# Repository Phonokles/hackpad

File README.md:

# ascii-emotion-controller

A macropad for switching the expressions of my ASCII character while
streaming or recording. Built for Hack Club Stardance.

## Why

I have a small face tracking app that renders an ASCII face and animates it
from my webcam and mic. The face sits on top of my stream in OBS, so the
browser window is never the focused one. Keystrokes always land somewhere
else, no matter what I press.

So the hackpad does not show up as a keyboard. It sends lines over USB
serial instead, and the page reads them with WebSerial. That works no matter
which window is in front.

## What is in it

* Seeed XIAO RP2040
* 3 Cherry MX switches
* 1 EC11 rotary encoder with push button
* 1 SSD1306 OLED, 0.91 inch, 128x32, over I2C
* 74 x 75 mm, two layers, solid ground pour
* Case is two printed parts, held together with M3 heatset inserts

Full part list in [BOM.csv](BOM.csv).

## Case

The base is a 8 mm tray with four 3 mm posts that hold the board off the
floor so the solder joints have room. The top plate is 1.5 mm thick around
the switch cutouts, which is what MX clips need to snap in.

## Controls

| Input | does |
| --- | --- |
| SW1 | normal `[+_+]` |
| SW2 | laughing `[*_*]` |
| SW3 | bored `[-_-]` |
| Turn wheel | opens the menu on the OLED |
| Press wheel in menu | confirm selection |
| Hold wheel | mouth keeps moving even when I am quiet |

The menu has auto, normal, laughing, bored, record and transparent.

## Protocol

The XIAO sends one line per event:

```
READY:hackpad
DOWN:btn1
UP:btn1
EXPR:laughing
ACT:record
```

## Repo layout

```
production/
  gerbers/      board files for the fab
  cad/          case as STEP and STL
  firmware/     boot.py and code.py
hardware/       KiCad project
web/            the face tracking page
docs/           renders and photos
BOM.csv
```

## Setup

### Firmware

Flash CircuitPython onto the XIAO, then copy `boot.py` and `code.py` from
`production/firmware/` to the root of the CIRCUITPY drive.

From the Adafruit library bundle into `CIRCUITPY/lib/`:

* `adafruit_displayio_ssd1306.mpy`
* `adafruit_display_text/`

`keypad`, `rotaryio` and `usb_cdc` are already built in.

### Website

Needs a local server, because ES modules fail CORS over `file://`:

```
cd web
python -m http.server 8000
```

Open `http://localhost:8000` and click the connect button in the bottom
right corner. The browser asks for permission once and remembers it.

Needs Chromium or Chrome. Firefox has no WebSerial.

On Linux your user needs access to `/dev/ttyACM0`. On Arch:

```
sudo usermod -aG uucp $USER
```

Log out and back in afterwards.

### Hardware

KiCad 9 or newer, project in `hardware/`.

The case prints without support. STEP files are in `production/cad/` if you
want to change something, STL next to them for printing straight away.

## Known things

* The OBS browser source cannot do WebSerial. The page runs in a Chromium
  window and OBS picks it up with a window capture.
* Chromium freezes tabs that are fully hidden, so the window has to stay
  visible somewhere. I keep it on its own workspace.
* The display footprint is drawn for a 1.3 inch module but a 0.91 inch one
  goes in. The four pads line up, the printed outline is just a bit large.

## License

MIT

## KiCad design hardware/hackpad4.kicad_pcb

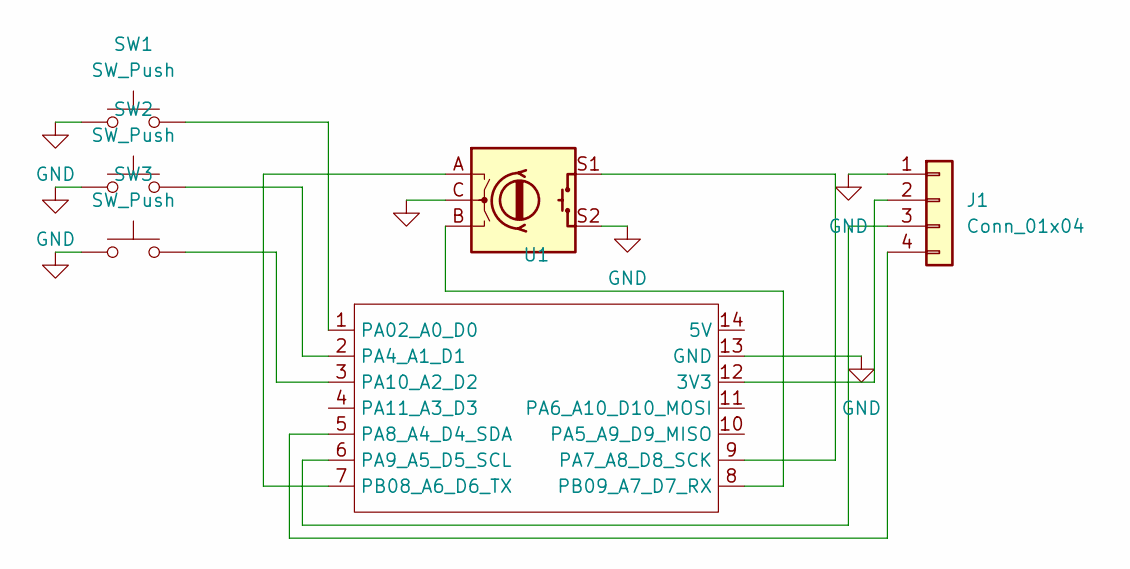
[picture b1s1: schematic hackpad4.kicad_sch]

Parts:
J1: Conn_01x04; FanPinHeader_1x04_P2.54mm_Vertical
SW1, SW2, SW3: SW_Push; SW_Cherry_MX_1.00u_PCB
SW4: RotaryEncoder_Switch; RotaryEncoder_Alps_EC11E-Switch_Vertical_H20mm
U1: MOUDLE-SEEEDUINO-XIAO; XIAO-Generic-Hybrid-14P-2.54-21X17.8MM

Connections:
GND: J1.1, SW1.1, SW2.1, SW3.1, SW4.C, SW4.S2, U1.13 (GND)
unnamed: J1.2, U1.12 (3V3)
unnamed: J1.3, U1.6 (PA9_A5_D5_SCL)
unnamed: J1.4, U1.5 (PA8_A4_D4_SDA)
unnamed: SW1.2, U1.1 (PA02_A0_D0)
unnamed: SW2.2, U1.2 (PA4_A1_D1)
unnamed: SW4.S1, U1.9 (PA7_A8_D8_SCK)
unnamed: SW3.2, U1.3 (PA10_A2_D2)
unnamed: SW4.A, U1.7 (PB08_A6_D6_TX)
unnamed: SW4.B, U1.8 (PB09_A7_D7_RX)

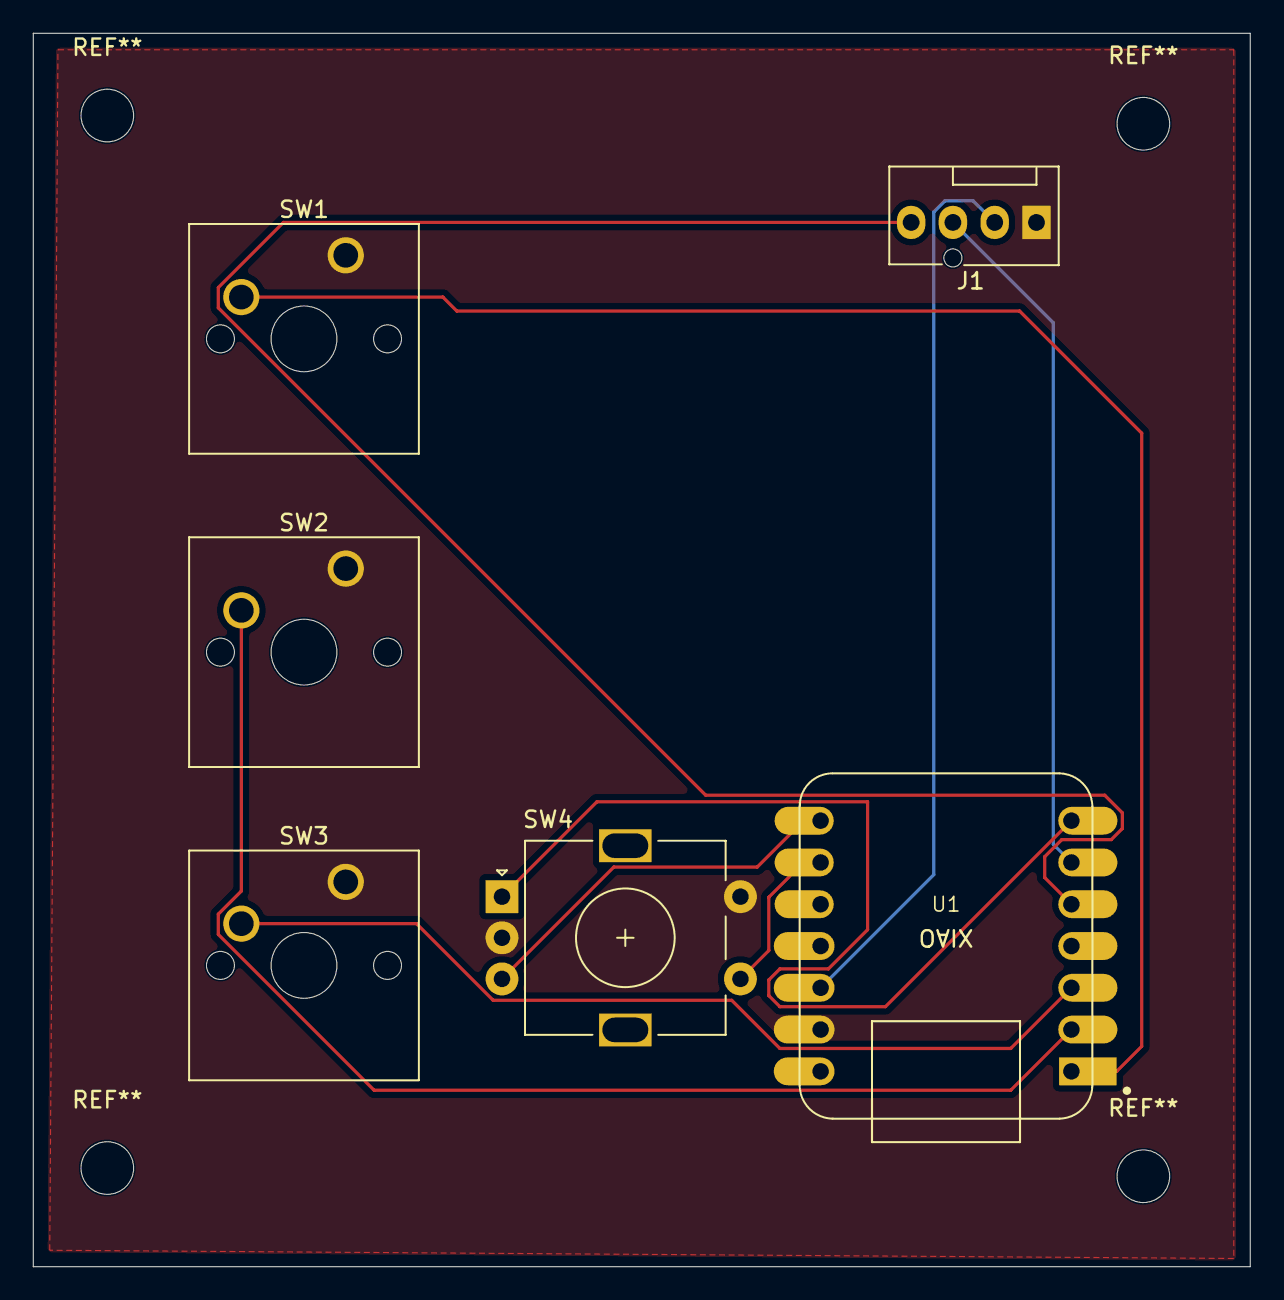
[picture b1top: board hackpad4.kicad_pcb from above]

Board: 2 copper layers, 74.0 x 75.0 mm, 6 parts (0 on the bottom side), 10 nets.

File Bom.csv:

Reference,Quantity,Component,Description,Footprint,Notes
U1,1,Seeed XIAO RP2040,Main microcontroller board,XIAO-Generic-Hybrid-14P,Through hole headers
SW1-SW3,3,Cherry MX switch,Mechanical key switch,SW_Cherry_MX_1.00u_PCB,19.05 mm spacing
SW4,1,ALPS EC11 rotary encoder,Incremental encoder with push button,RotaryEncoder_Alps_EC11E-Switch_Vertical_H20mm,5 pins plus 2 mounting tabs
J1,1,Pin header 1x04 2.54 mm,Connector for the OLED module,PinHeader_1x04_P2.54mm_Vertical,Pin order GND-VCC-SCL-SDA
J1,1,SSD1306 OLED 0.91 inch,128x32 I2C display module,-,Plugs into J1
-,3,Keycap MX,Caps for the three switches,-,-
-,1,Encoder knob,Knob for the EC11 shaft,-,6 mm shaft
-,4,M3 heatset insert,Threaded insert for the case,-,4.7 mm hole 4 mm deep
-,4,M3 screw 8 mm,Holds the top plate to the base,-,3.4 mm clearance holes
-,1,PCB,74 x 75 mm two layer board,-,See production/gerbers
-,1,Case base,2D printed,-,production/cad
-,1,Case top plate,3D printed,-,1.5 mm around switch cutouts
-,1,USB-C cable,Data cable for the XIAO,-,Must carry data not only power
